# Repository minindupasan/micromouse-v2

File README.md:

# Micromouse V2

This repository contains the design files, firmware, and documentation for a maze-solving car built using the STM32F103C8T6 microcontroller. The car is equipped with sensors, motors, and communication interfaces to autonomously navigate and solve mazes.

---

## Table of Contents
1. [Overview](#overview)
2. [Hardware Components](#hardware-components)
3. [PCB Design](#pcb-design)
4. [Firmware](#firmware)
5. [Communication Interfaces](#communication-interfaces)
6. [Setup and Usage](#setup-and-usage)
7. [Repository Structure](#repository-structure)
8. [License](#license)

---

## Overview

The maze-solving car is an autonomous robot designed to navigate through a maze using sensor data and decision-making algorithms. The car is built around the STM32F103C8T6 microcontroller and features the following key functionalities:
- **Maze Navigation**: Uses the MPU6050 (IMU) and VL53L0X (Time-of-Flight sensor) for orientation and distance measurement.
- **Motor Control**: TB6612FNG motor driver controls N20 motors for precise movement.
- **Debugging**: SSD1306 OLED display and UART communication for real-time debugging.
- **User Interface**: Three push buttons for menu selection and interaction.
- **Communication**: USB Type-C and UART interfaces for firmware updates and debugging.

---

## Hardware Components

### Microcontroller
- **STM32F103C8T6**: ARM Cortex-M3 based microcontroller for control and decision-making.

### Sensors
- **MPU6050**: 6-axis IMU for orientation and motion tracking.
- **VL53L0X**: Time-of-Flight (ToF) sensor for distance measurement.

### Motor Driver
- **TB6612FNG**: Dual motor driver for controlling N20 motors.

### Power Management
- **AMS1117**: 3.3V voltage regulator.
- **L7806CV**: 6V voltage regulator.
- **L7805CV**: 5V voltage regulator.

### Communication
- **USB Type-C**: For USB communication with the STM32.
- **UART Terminals**: For debugging and communication.
- **SWD (Serial Wire Debug)**: For STLink compatibility and firmware flashing.

### Other Components
- **N20 Motors**: Geared DC motors for movement.
- **SSD1306 OLED Display**: For debugging and status display.
- **Push Buttons**: Three buttons for menu selection and control.
- **SPDT Switch**: For boot mode selection.
- **Crystal Oscillators**:
  - **HSE**: 8 MHz (ABLS2-8.000MHZ-D4Y-T).
  - **LSE**: 32.768 kHz (ABS07-32.768KHZ-T).

> [!NOTE]
> The PCB design is optimized for 0805 SMD components, ensuring a compact and efficient layout.

---

## PCB Design

The PCB design files are available in the `hardware/` directory. The design includes:
- Schematic and layout files (e.g., KiCad, Altium, or Eagle).
- Gerber files for manufacturing.
- Bill of Materials (BOM) for component sourcing.

### Key Features of the PCB:
- Compact design optimized for maze-solving applications.
- Integrated power management with multiple voltage regulators.
- Debugging interfaces (UART, SWD, OLED display).
- USB Type-C for easy connectivity.

> [!TIP]
> Use the provided Gerber files for manufacturing the PCB. Ensure the manufacturer supports 2-layer boards with 1.6mm thickness.

---

## Firmware

The firmware for the maze-solving car is written in C using the STM32 HAL library. The code is located in the `firmware/` directory and includes the following features:
- **Maze Navigation Algorithm**: Implements wall-following or other maze-solving logic.
- **Sensor Integration**: Reads data from MPU6050 and VL53L0X sensors.
- **Motor Control**: Controls N20 motors using the TB6612FNG driver.
- **Debugging**: Displays real-time data on the SSD1306 OLED display.
- **User Interface**: Handles input from the push buttons.

### Dependencies
- STM32CubeMX for peripheral configuration.
- STM32 HAL library for hardware abstraction.

> [!IMPORTANT]
> Ensure the correct version of the STM32 HAL library is used to avoid compatibility issues.

> [!WARNING]
> Do not modify the STM32CubeMX configuration files manually. Always regenerate them using STM32CubeMX after making changes.

---

## Communication Interfaces

The car supports multiple communication interfaces for debugging and control:
1. **USB Type-C**: Used for firmware updates and communication with a PC.
2. **UART**: Serial communication for debugging and data logging.
3. **SWD**: For flashing firmware and debugging using STLink.

> [!TIP]
> Use a USB-to-UART converter for easy debugging via UART.

> [!CAUTION]
> Ensure the baud rate for UART communication matches between the car and the debugging tool.

---

## Setup and Usage

### Prerequisites
- STM32CubeIDE or any compatible IDE for firmware development.
- STLink or similar debugger for flashing the firmware.
- USB Type-C cable for communication and power.

### Steps to Use
1. **Flash the Firmware**:
   - Connect the STLink to the SWD terminals.
   - Open the project in STM32CubeIDE and flash the firmware.

2. **Power the Car**:
   - Connect a 7-12V power supply to the voltage regulators.

3. **Debugging**:
   - Use the UART terminals or OLED display for real-time debugging.

4. **Maze Navigation**:
   - Place the car in a maze and use the push buttons to start the navigation algorithm.

> [!WARNING]
> Double-check the polarity of the power supply connection to prevent damage to the PCB.

---

## Repository Structure
```
maze-solving-car-pcb/
├── firmware/                  # STM32 firmware source code
│   ├── Inc/                   # Header files
│   ├── Src/                   # Source files
│   └── STM32CubeMX/           # CubeMX configuration files
├── hardware/                  # PCB design files
│   ├── schematics/            # Schematic diagrams
│   ├── layout/                # PCB layout files
│   └── gerber/                # Gerber files for manufacturing
├── images/                    # Images and diagrams
├── docs/                      # Documentation and datasheets
└── README.md                  # This file
```

---

## License
This project is licensed under the MIT License. See the [LICENSE](LICENSE) file for details.

---

## Acknowledgments
- STMicroelectronics for the STM32 HAL library.
- Contributors to open-source hardware and software tools.

For questions or contributions, please open an issue or submit a pull request.

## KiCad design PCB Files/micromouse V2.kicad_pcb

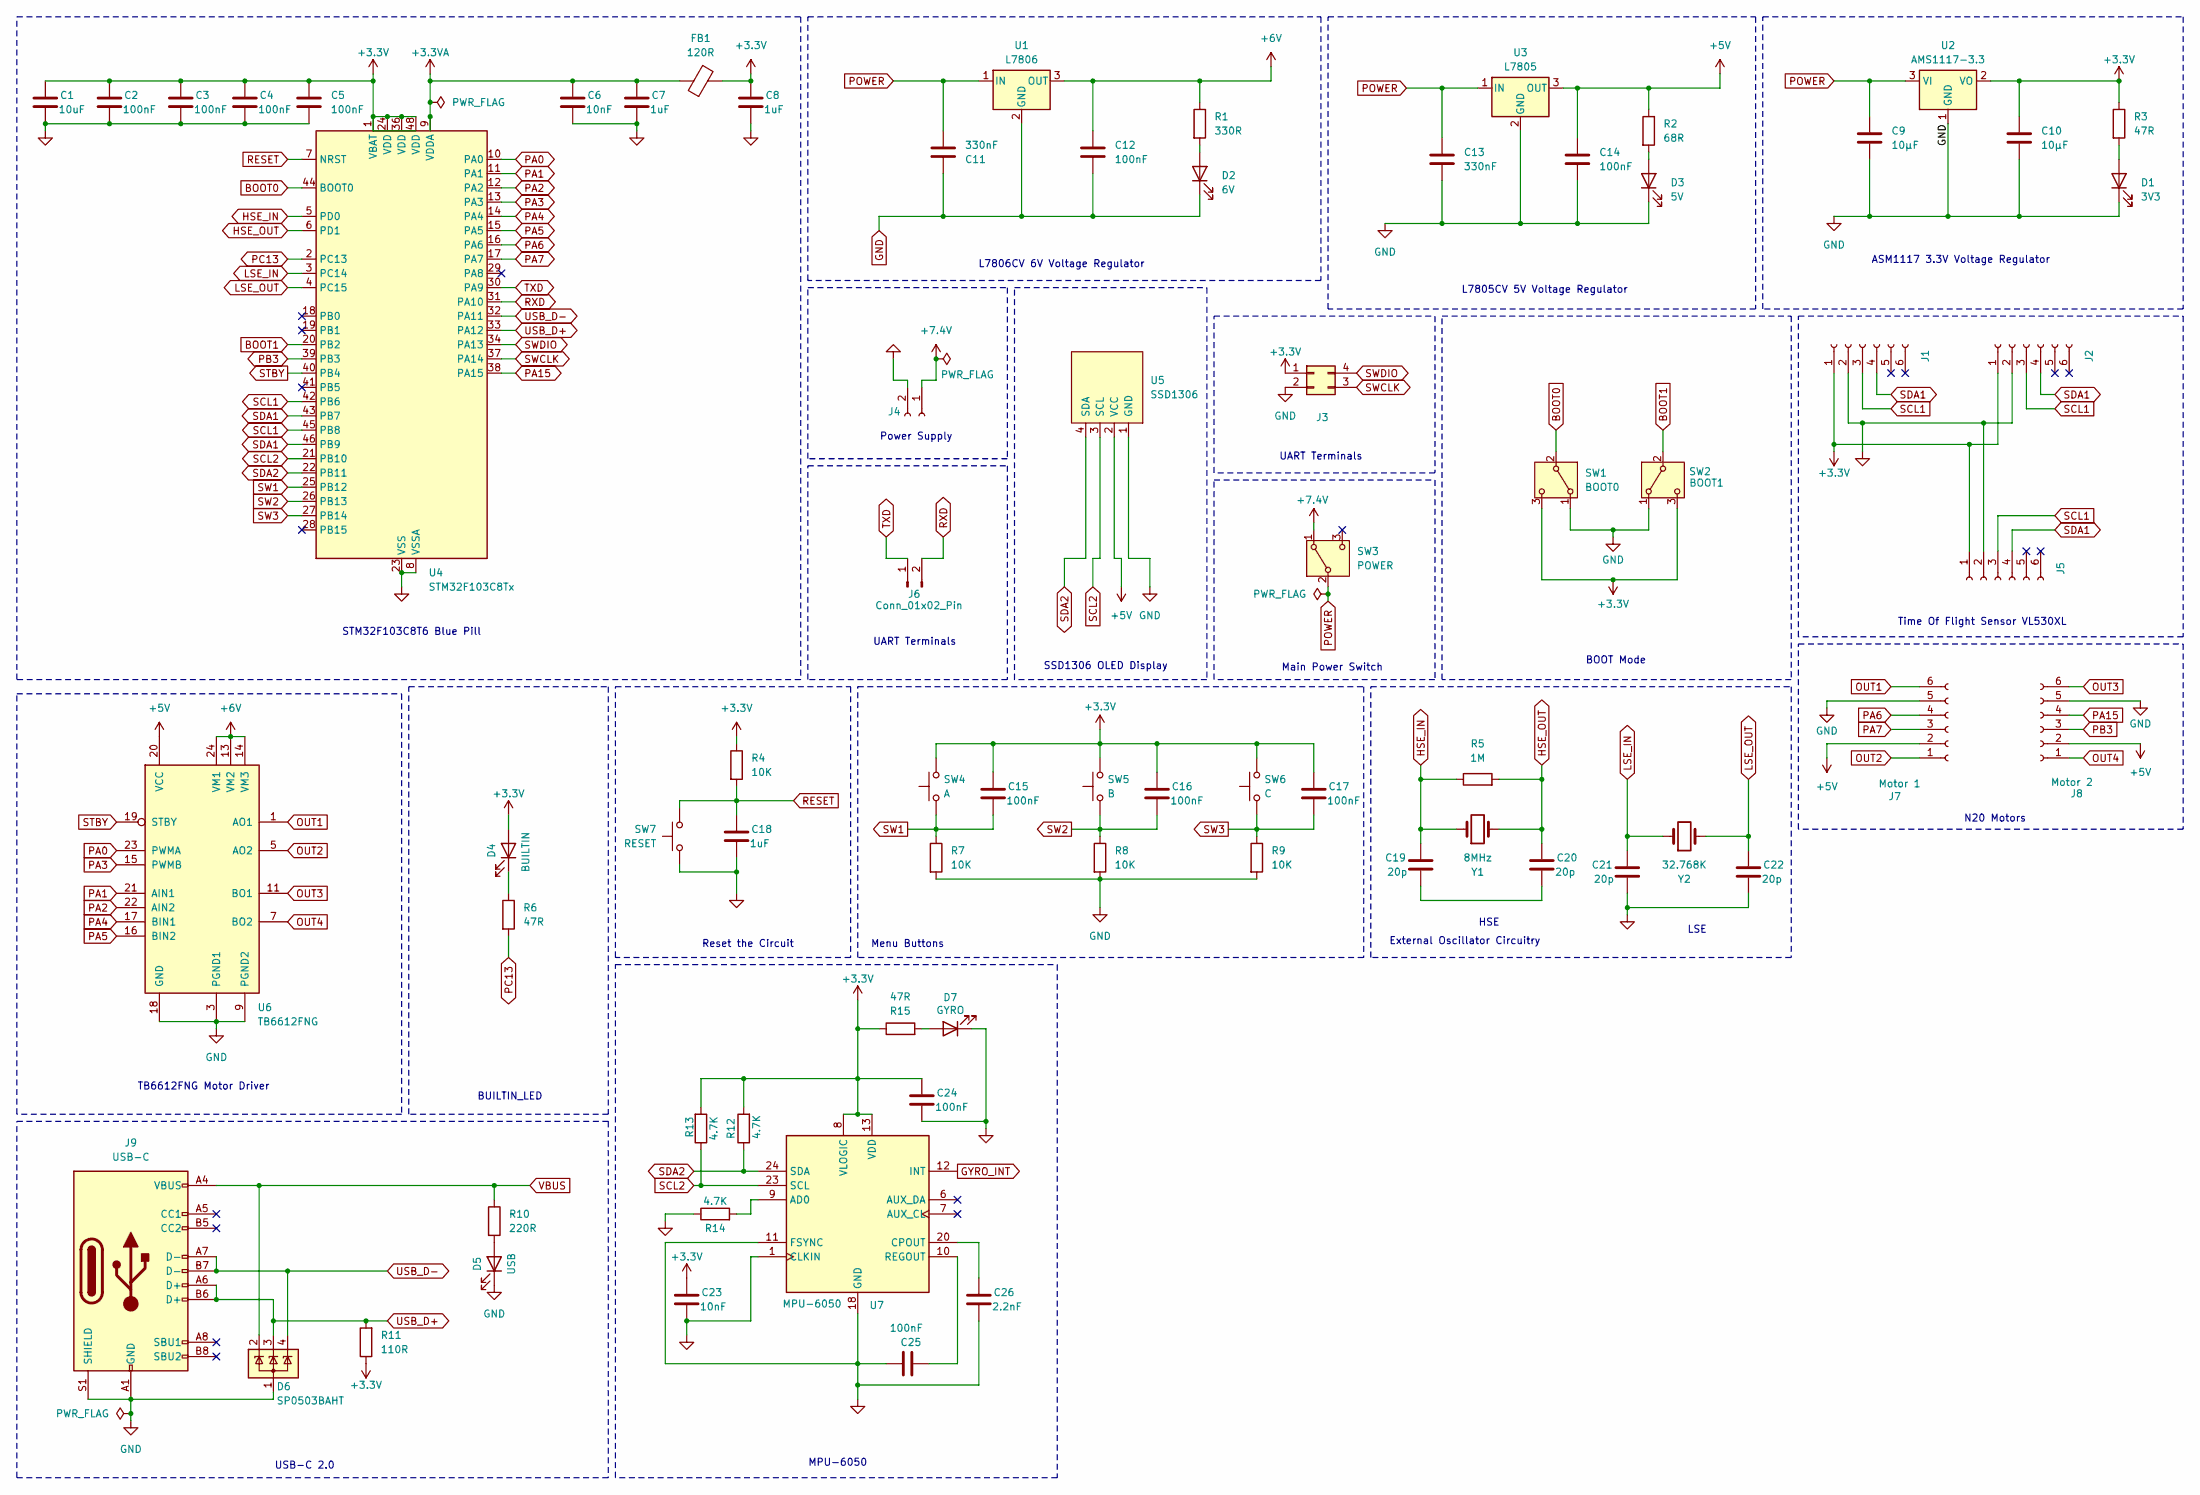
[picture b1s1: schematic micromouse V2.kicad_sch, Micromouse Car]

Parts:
C1: 10uF; C_0805_2012Metric; JLCPCB Part# C1713
C2, C3, C4, C5, C12, C14, C15, C16, C17, C24, C25: 100nF; C_0805_2012Metric; JLCPCB Part# C520082
C6, C23: 10nF; C_0805_2012Metric; JLCPCB Part# C519909
C7, C8, C18: 1uF; C_0805_2012Metric; JLCPCB Part# C24123
C9, C10: 10µF; C_0805_2012Metric; JLCPCB Part# C95841
C11, C13: 330nF; C_0805_2012Metric; JLCPCB Part# C318723
C19, C20, C21, C22: 20p; C_0805_2012Metric; JLCPCB Part# C1798
C26: 2.2nF; C_0805_2012Metric; JLCPCB Part# C519912
D1: 3V3; LED_0805_2012Metric; JLCPCB Part# C2297
D2: 6V; LED_0805_2012Metric; JLCPCB Part# C2297
D3: 5V; LED_0805_2012Metric; JLCPCB Part# C2297
D4: BUILTIN; LED_0805_2012Metric; JLCPCB Part# C2297
D5: USB; LED_0805_2012Metric; JLCPCB Part# C2297
D6: SP0503BAHT; SOT-143; JLCPCB Part# C7074
D7: GYRO; LED_0805_2012Metric; JLCPCB Part# C2297
FB1: 120R; L_0805_2012Metric; JLCPCB Part# C88990
J1, J2, J5: TOF1; PinSocket_1x06_P2.54mm_Vertical
J3: Conn_02x02_Counter_Clockwise; PinHeader_2x02_P2.54mm_Vertical
J4: BATT; JST_XH_B2B-XH-A_1x02_P2.50mm_Vertical; JLCPCB Part# C265283
J6: Conn_01x02_Pin; PinHeader_1x02_P2.54mm_Vertical
J7: Motor 1; JST_XH_B6B-XH-A_1x06_P2.50mm_Vertical; JLCPCB Part# C265366
J8: Motor 2; JST_XH_B6B-XH-A_1x06_P2.50mm_Vertical; JLCPCB Part# C265366
J9: USB-C; USB_C_Receptacle_HRO_TYPE-C-31-M-12; JLCPCB Part# C165948
R1: 330R; R_0805_2012Metric; JLCPCB Part# C17630
R2: 68R; R_0805_2012Metric; JLCPCB Part# C17802
R3, R6, R15: 47R; R_0805_2012Metric; JLCPCB Part# C17714
R4, R7, R8, R9: 10K; R_0805_2012Metric; JLCPCB Part# C17414
R5: 1M; R_0805_2012Metric; JLCPCB Part# C17514
R10: 220R; R_0805_2012Metric; JLCPCB Part# C17557
R11: 110R; R_0805_2012Metric; JLCPCB Part# C17423
R12, R13, R14: 4.7K; R_0805_2012Metric; JLCPCB Part# C17673
SW1: BOOT0; SW_SS12D07VG4; JLCPCB Part# C2939726
SW2: BOOT1; SW_SS12D07VG4; JLCPCB Part# C2939726
SW3: POWER; SW_SS12D07VG4; JLCPCB Part# C2939726
SW4: A; SW_PUSH_6mm_H13mm; JLCPCB Part# C7470131
SW5: B; SW_PUSH_6mm_H13mm; JLCPCB Part# C7470131
SW6: C; SW_PUSH_6mm_H13mm; JLCPCB Part# C7470131
SW7: RESET; SW_PUSH_6mm_H13mm; JLCPCB Part# C7470131
U1: L7806; TO-220-3_Vertical
U2: AMS1117-3.3; SOT-223-3_TabPin2; JLCPCB Part# C6186
U3: L7805; TO-220-3_Vertical
U4: STM32F103C8Tx; LQFP-48_7x7mm_P0.5mm; JLCPCB Part# C8734
U5: SSD1306; 128x64OLED
U6: TB6612FNG; SSOP-24_5.3x8.2mm_P0.65mm; JLCPCB Part# C141517
U7: MPU-6050; InvenSense_QFN-24_4x4mm_P0.5mm; JLCPCB Part# C24112
Y1: 8MHz; Crystal_ABLS2-8.000MHZ-D4Y-T; JLCPCB Part# C596832
Y2: 32.768K; XTAL_ABS07-32.768KHZ-T; JLCPCB Part# C130253

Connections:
+3.3V: C1.1, C2.1, C3.1, C4.1, C5.1, C8.1, C10.1, C15.1, C16.1, C17.1, C23.1, C24.1, D4.2 (A), FB1.2, J1.1, J2.1, J3.1, J5.1, R3.1, R4.1, R11.1, R12.2, R13.2, R15.1, SW1.3 (C), SW2.3 (C), SW4.2, SW5.2, SW6.2, U2.2 (VO), U4.1 (VBAT), U4.24 (VDD), U4.36 (VDD), U4.48 (VDD), U7.8 (VLOGIC), U7.13 (VDD)
+3.3VA: C6.1, C7.1, FB1.1, U4.9 (VDDA)
+5V: C14.1, J7.2, J8.2, R2.1, U3.3 (OUT), U5.2 (VCC), U6.20 (VCC)
+6V: C12.1, R1.1, U1.3 (OUT), U6.13 (VM2), U6.14 (VM3), U6.24 (VM1)
+7.4V: J4.1, SW3.1 (A)
BOOT0: SW1.2 (B), U4.44 (BOOT0)
BOOT1: SW2.2 (B), U4.20 (PB2)
GND: C1.2, C2.2, C3.2, C4.2, C5.2, C6.2, C7.2, C8.2, C9.2, C10.2, C11.1, C12.2, C13.2, C14.2, C18.2, C21.2, C22.2, C23.2, C24.2, C25.1, C26.2, D1.1 (K), D2.1 (K), D3.1 (K), D5.1 (K), D6.1 (A), D7.1 (K), J1.2, J2.2, J3.2, J4.2, J5.2, J7.5, J8.5, J9.A1 (GND), J9.A12 (GND), J9.B1 (GND), J9.B12 (GND), J9.S1 (SHIELD), R7.2, R8.2, R9.2, R14.1, SW1.1 (A), SW2.1 (A), SW7.1, U1.2 (GND), U2.1 (GND), U3.2 (GND), U4.8 (VSSA), U4.23 (VSS), U4.35 (VSS), U4.47 (VSS), U5.1 (GND), U6.3 (PGND1), U6.4 (PGND1), U6.9 (PGND2), U6.10 (PGND2), U6.18 (GND), U7.1 (CLKIN), U7.11 (FSYNC), U7.18 (GND)
GYRO_INT: U7.12 (INT)
HSE_IN: C19.1, R5.1, U4.5 (PD0), Y1.1
HSE_OUT: C20.1, R5.2, U4.6 (PD1), Y1.2
LSE_IN: C21.1, U4.3 (PC14), Y2.1
LSE_OUT: C22.1, U4.4 (PC15), Y2.2
unnamed: C19.2, C20.2
unnamed: D1.2 (A), R3.2
unnamed: D2.2 (A), R1.2
unnamed: D3.2 (A), R2.2
unnamed: D4.1 (K), R6.1
unnamed: D5.2 (A), R10.2
unnamed: D7.2 (A), R15.2
unnamed: R14.2, U7.9 (AD0)
unnamed: C26.1, U7.20 (CPOUT)
unnamed: C25.2, U7.10 (REGOUT)
OUT1: J7.6, U6.1 (AO1), U6.2 (AO1)
OUT2: J7.1, U6.5 (AO2), U6.6 (AO2)
OUT3: J8.6, U6.11 (BO1), U6.12 (BO1)
OUT4: J8.1, U6.7 (BO2), U6.8 (BO2)
PA0: U4.10 (PA0), U6.23 (PWMA)
PA1: U4.11 (PA1), U6.21 (AIN1)
PA2: U4.12 (PA2), U6.22 (AIN2)
PA3: U4.13 (PA3), U6.15 (PWMB)
PA4: U4.14 (PA4), U6.17 (BIN1)
PA5: U4.15 (PA5), U6.16 (BIN2)
PA6: J7.4, U4.16 (PA6)
PA7: J7.3, U4.17 (PA7)
PA15: J8.4, U4.38 (PA15)
PB3: J8.3, U4.39 (PB3)
PC13: R6.2, U4.2 (PC13)
POWER: C9.1, C11.2, C13.1, SW3.2 (B), U1.1 (IN), U2.3 (VI), U3.1 (IN)
RESET: C18.1, R4.2, SW7.2, U4.7 (NRST)
RXD: J6.2, U4.31 (PA10)
SCL1: J1.3, J2.3, J5.3, U4.42 (PB6), U4.45 (PB8)
SCL2: R13.1, U4.21 (PB10), U5.3 (SCL), U7.23 (SCL)
SDA1: J1.4, J2.4, J5.4, U4.43 (PB7), U4.46 (PB9)
SDA2: R12.1, U4.22 (PB11), U5.4 (SDA), U7.24 (SDA)
STBY: U4.40 (PB4), U6.19 (STBY)
SW1: C15.2, R7.1, SW4.1, U4.25 (PB12)
SW2: C16.2, R8.1, SW5.1, U4.26 (PB13)
SW3: C17.2, R9.1, SW6.1, U4.27 (PB14)
SWCLK: J3.3, U4.37 (PA14)
SWDIO: J3.4, U4.34 (PA13)
TXD: J6.1, U4.30 (PA9)
USB_D+: D6.3 (K), J9.A6 (D+), J9.B6 (D+), R11.2, U4.33 (PA12)
USB_D-: D6.4 (K), J9.A7 (D-), J9.B7 (D-), U4.32 (PA11)
VBUS: D6.2 (K), J9.A4 (VBUS), J9.A9 (VBUS), J9.B4 (VBUS), J9.B9 (VBUS), R10.1
XSHUT1: J1.6, U4.29 (PA8)
XSHUT2: J2.6, U4.19 (PB1)
XSHUT3: J5.6, U4.18 (PB0)

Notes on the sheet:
Main Power Switch
Menu Buttons
Time Of Flight Sensor VL530XL
SSD1306 OLED Display
UART Terminals
ASM1117 3.3V Voltage Regulator
Power Supply
LSE
USB-C 2.0
STM32F103C8T6 Blue Pill
External Oscillator Circuitry
BUILTIN_LED
Reset the Circuit
L7806CV 6V Voltage Regulator
TB6612FNG Motor Driver
HSE
MPU-6050
N20 Motors
BOOT Mode
L7805CV 5V Voltage Regulator

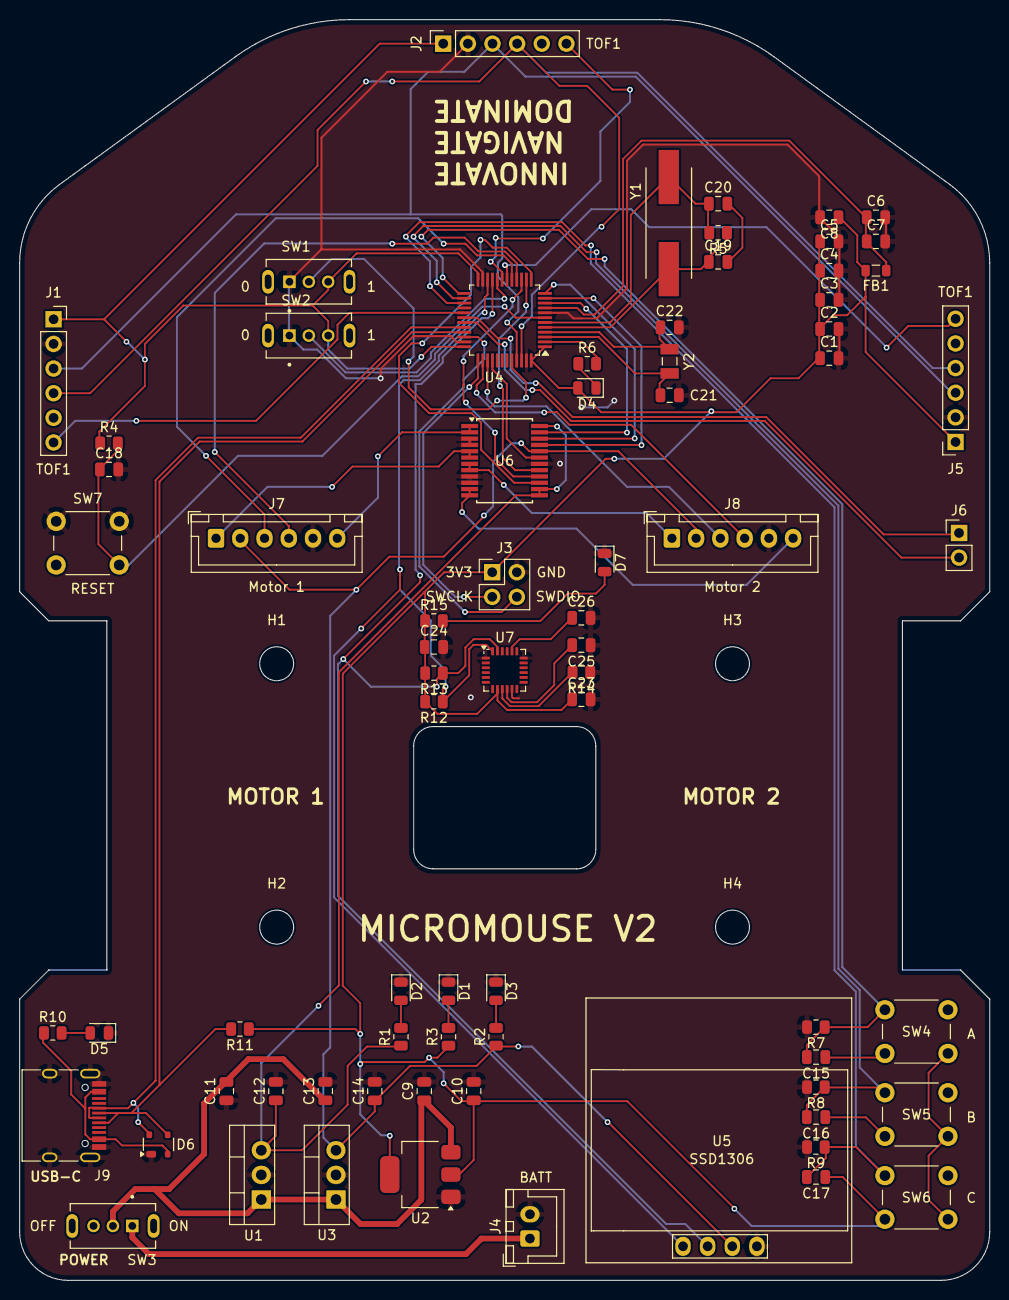
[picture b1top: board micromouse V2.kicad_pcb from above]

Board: 2 copper layers, 100.0 x 130.0 mm, 78 parts (0 on the bottom side), 57 nets.

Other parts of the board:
H1, H2, H3, H4: MountingHole_3.5mm

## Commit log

2024-12-14 Added PCB files for Micromouse project
2024-12-14 Assigned HSE and LSE Oscillators
    HSE - ABLS2-8.000MHZ-D4Y-T
    LSE - ABS07-32.768KHZ-T
2024-12-15 Fixed PCB Layout
2024-12-15 default
2024-12-30 Fixed
2024-12-30 Flipped TOF
2024-12-30 asdasd
2025-02-03 Removed unused files
2025-02-03 Modified the text in pcb
2025-02-03 Rename Screenshot 2025-02-03 at 18.57.03.png to pcb-front
2025-02-03 Rename Screenshot 2025-02-03 at 19.06.43.png to 3d-1
2025-02-03 Rename Screenshot 2025-02-03 at 18.57.51.png to 3d-2
2025-02-03 Rename pcb to images/pcb
2025-02-03 Rename 3d-2 to images/3d-2
2025-02-03 Rename 3d-1 to 3d-1.png
2025-02-03 Rename 3d-1.png to images/3d-1.png
2025-02-03 Rename 3d-2 to 3d-2.png
2025-02-03 Rename pcb to pcb.png
